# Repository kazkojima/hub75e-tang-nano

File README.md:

## HUB75E driver with Tang Nano FPGA and WiFi adaptor with M5ATOM

The driver part by Tang Nano for 64x64 LED panels with the HUB75E
interface is based on https://github.com/shinyblink/sled-fpga-hub75.

The WiFi part by M5ATOM is an esp-idf application. It receives RGB565
udp packet format of [LED master](https://github.com/spectrenoir06/LED_master)
and writes the frame data to FPGA with SPI.

The main SPI should assert CS, write 64x64(4096) RGB555 words and negate CS
with mode0. The HUB75E panel is divided to 2 64x32 planes and the SPI data
should be organized as

```
   word 0, word 2048, word 1, word 2049, ... , word 2047, word 4095
```

so as to get 2 words for both panels at the same time with one 32-bit data
from BRAM.

This driver does nothing to sync frame read/write from/to BRAM, the images
displayed on the top and bottom panels may be out of sync.

I use 16Mhz clock for the base clock to minimize the artifacts on my panel,
though there may be panels which can be ok with the higher clocks. SPI
requires the base clock which is at least x4 the SCLK, i.e. the maximal
SCLK is limited by 4Mhz for the 16Mhz base clock.

All sources are covered by ISC License, except src/hub75e.{sdc,cst} files
which are generated files by GOWIN IDE.

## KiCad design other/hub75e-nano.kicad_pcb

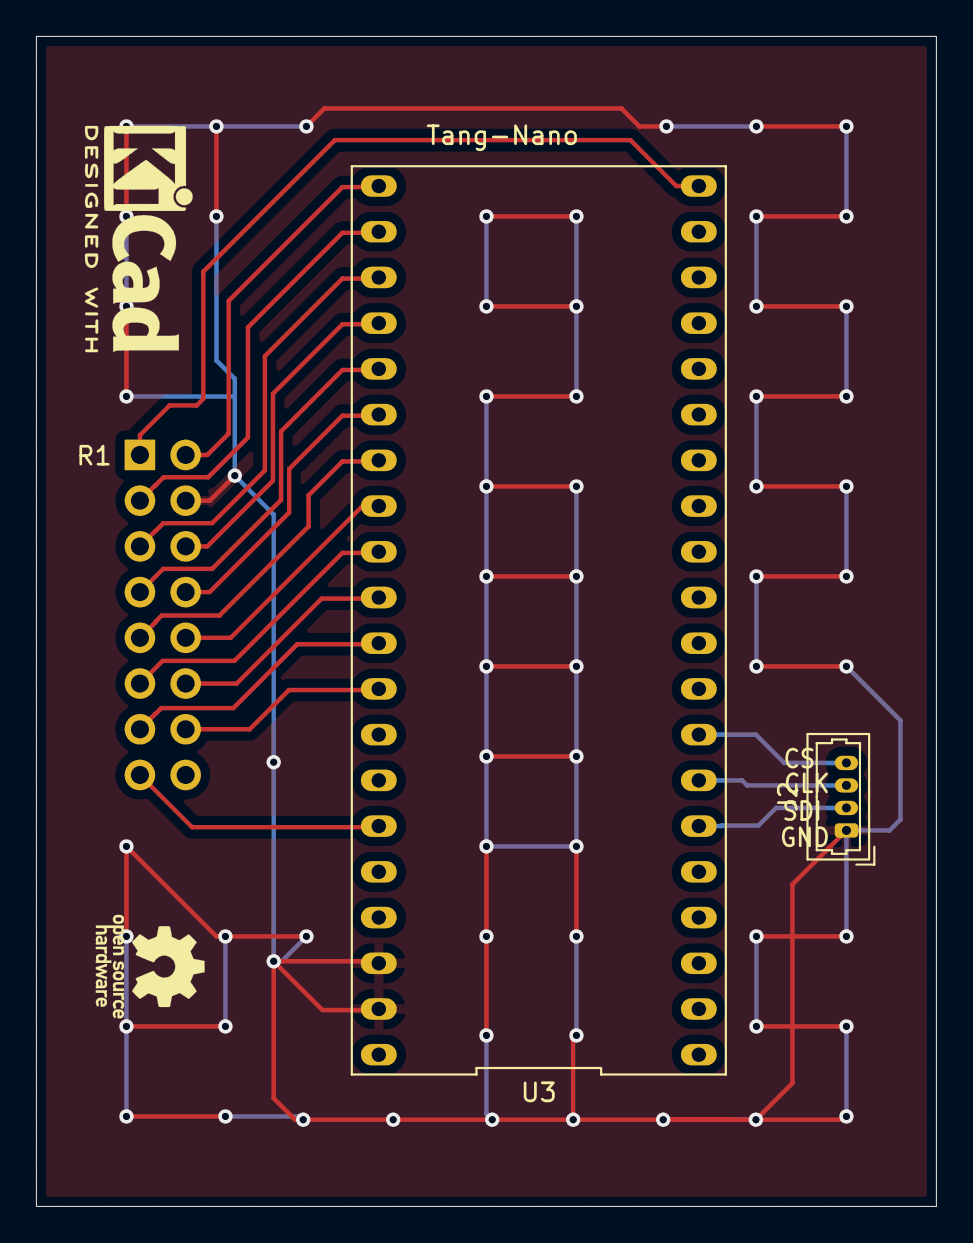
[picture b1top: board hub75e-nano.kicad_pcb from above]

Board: 2 copper layers, 50.0 x 65.0 mm, 3 parts (1 on the bottom side), 19 nets.

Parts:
J1: Conn_02x08_Odd_Even; PinSocket_2x08_P2.54mm_Vertical
J2: Conn_01x04; Molex_PicoBlade_53047-0410_1x04_P1.25mm_Vertical
U3: Tang-Nano; DIP-40_700_ELL

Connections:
/A: J1.9, U3.27
/B: J1.10, U3.28
/B1: J1.3, U3.22
/B2: J1.7, U3.25
/C: J1.11, U3.29
/CK: J1.13, U3.31
/D: J1.12, U3.30
/E: J1.8, U3.26
/G1: J1.2, U3.21
/G2: J1.6, U3.24
/OE: J1.15, U3.35
/R1: J1.1, U3.20
/R2: J1.5, U3.23
/SPI_CLK: J2.3, U3.7
/SPI_NCS: J2.4, U3.8
/SPI_SDI: J2.2, U3.6
/ST: J1.14, U3.32
GND: J1.4, J2.1, U3.38, U3.39
unnamed: U3.36, U3.37

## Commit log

2020-07-14 Initial commit.
2020-07-18 Add an example schematic.
2020-07-19 Drop pcb temporarily.
2020-07-19 Add a revised pcb layout.
2020-07-23 Add Lite support.
